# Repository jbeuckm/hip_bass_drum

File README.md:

hip_bass_drum
=============

Build a Eurorack version of Craig Anderton's Hip Bass Drum. This is a minor modification of Sebo's PCB posted in this thread: http://electro-music.com/forum/topic-28447.html

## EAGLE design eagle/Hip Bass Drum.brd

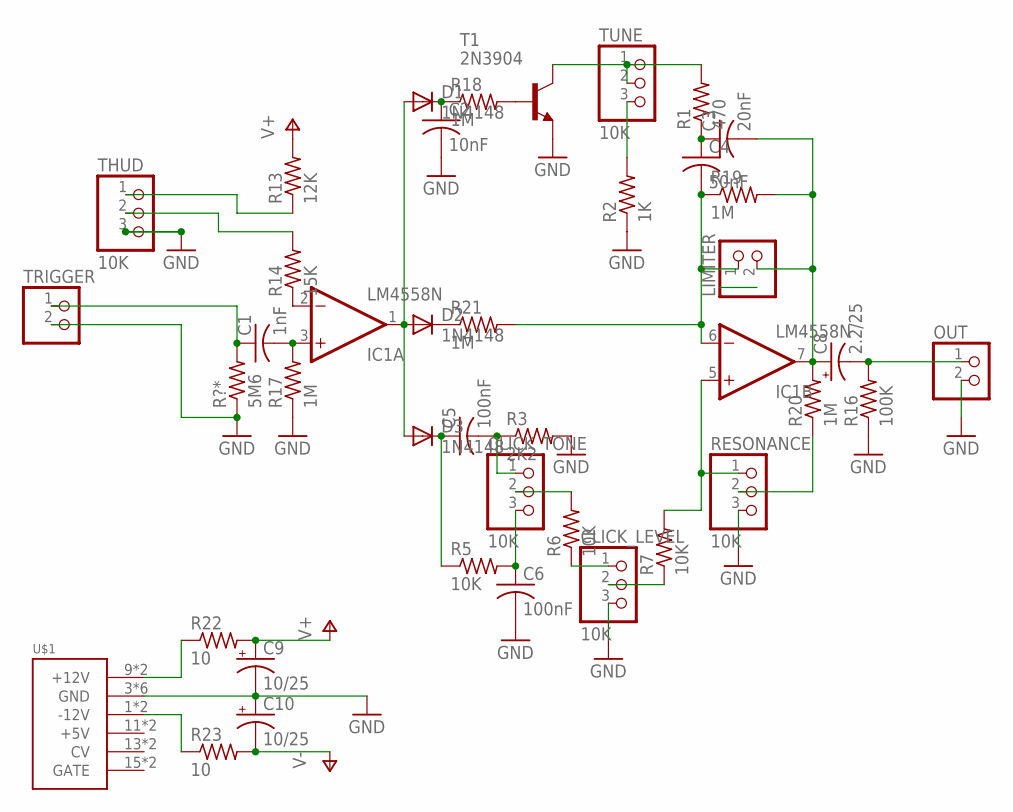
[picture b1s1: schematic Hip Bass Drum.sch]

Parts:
C1: 1nF; C025-030X050
C2: 10nF; C025-030X050
C3: 20nF; C025-030X050
C4: 50nF; C025-030X050
C5, C6: 100nF; C025-030X050
C8: 2.2/25; E2,5-7
C9, C10: 10/25; E2,5-7
CLICK_LEVEL: 10K; 1X03
CLICK_TONE: 10K; 1X03
D1, D2, D3: 1N4148; DO35-10
IC1: LM4558N; DIL08
LIMITER: PINHD-1X2; 1X02
OUT: PINHD-1X2; 1X02
R1: 470; 0207/10
R2: 1K; 0207/10
R3: 2K2; 0207/10
R5, R6, R7: 10K; 0207/10
R13: 12K; 0207/10
R14: 15K; 0207/10
R16: 100K; 0207/10
R17, R18, R19, R20, R21: 1M; 0207/10
R22, R23: 10; 0207/10
R?*: 5M6; 0207/10
RESONANCE: 10K; 1X03
T1: 2N3904; TO92
THUD: 10K; 1X03
TRIGGER: PINHD-1X2; 1X02
TUNE: 10K; 1X03
U$1: POWER; POWER_16

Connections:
GND: C2.2, C6.2, C9.-, C10.+, CLICK_LEVEL.3, OUT.2, R2.1, R3.2, R16.1, R17.1, R?*.1, RESONANCE.3, T1.3 (E), THUD.3, TRIGGER.2, U$1.3 (GND), U$1.4 (GND), U$1.5 (GND), U$1.6 (GND), U$1.7 (GND), U$1.8 (GND)
unnamed: C1.2, IC1.3 (+IN), R17.2
unnamed: C1.1, R?*.2, TRIGGER.1
unnamed: IC1.2 (-IN), R14.1
unnamed: R22.1, U$1.9 (+12V), U$1.10 (+12V)
unnamed: R23.1, U$1.1 (-12V), U$1.2 (-12V)
unnamed: R13.1, THUD.1
unnamed: R14.2, THUD.2
unnamed: C2.1, D1.C, R18.1
unnamed: R18.2, T1.2 (B)
unnamed: D1.A, D2.A, D3.A, IC1.1 (OUT)
unnamed: R1.2, T1.1 (C), TUNE.1, TUNE.2
unnamed: R2.2, TUNE.3
unnamed: C3.1, C4.1, R1.1
unnamed: C4.2, IC1.6 (-IN), LIMITER.1, R19.1, R21.2
unnamed: C3.2, C8.+, IC1.7 (OUT), LIMITER.2, R19.2, R20.2
unnamed: D2.C, R21.1
unnamed: C8.-, OUT.1, R16.2
unnamed: IC1.5 (+IN), R7.2, RESONANCE.1
unnamed: R20.1, RESONANCE.2
unnamed: C5.1, D3.C, R5.1
unnamed: C6.1, CLICK_TONE.3, R5.2
unnamed: C5.2, CLICK_TONE.1, R3.1
unnamed: CLICK_TONE.2, R6.2
unnamed: CLICK_LEVEL.1, R6.1
unnamed: CLICK_LEVEL.2, R7.1
V+: C9.+, IC1.8 (V+), R13.2, R22.2
V-: C10.-, IC1.4 (V-), R23.2

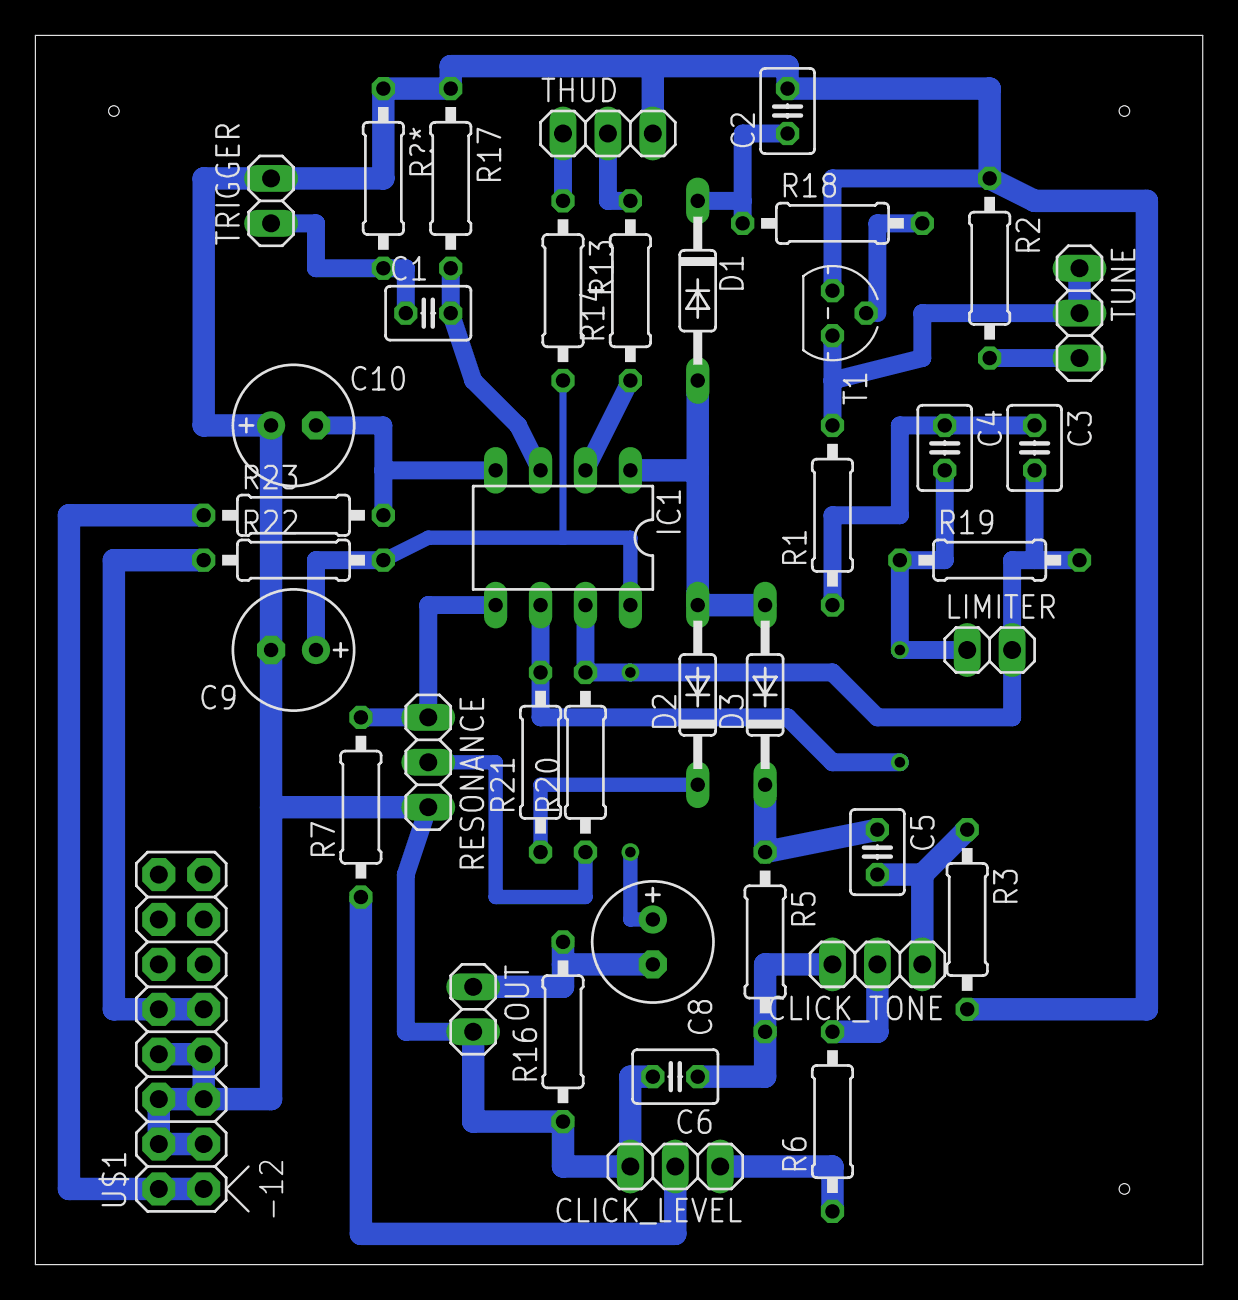
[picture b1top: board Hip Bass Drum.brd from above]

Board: 2 copper layers, 66.0 x 69.5 mm, 40 parts (0 on the bottom side), 28 nets.

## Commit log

2014-10-29 routed for eurorack
2014-10-30 removed the drill on the new trace
2014-11-01 thicker ground interconnects
2014-11-03 started a panel
2014-11-03 ignoring tempfiles
2014-11-04 chose panel width
2014-11-05 labeling knobs
2014-11-06 cleaned up machining
2014-11-07 input and output
2014-11-07 better trigger and output labels
